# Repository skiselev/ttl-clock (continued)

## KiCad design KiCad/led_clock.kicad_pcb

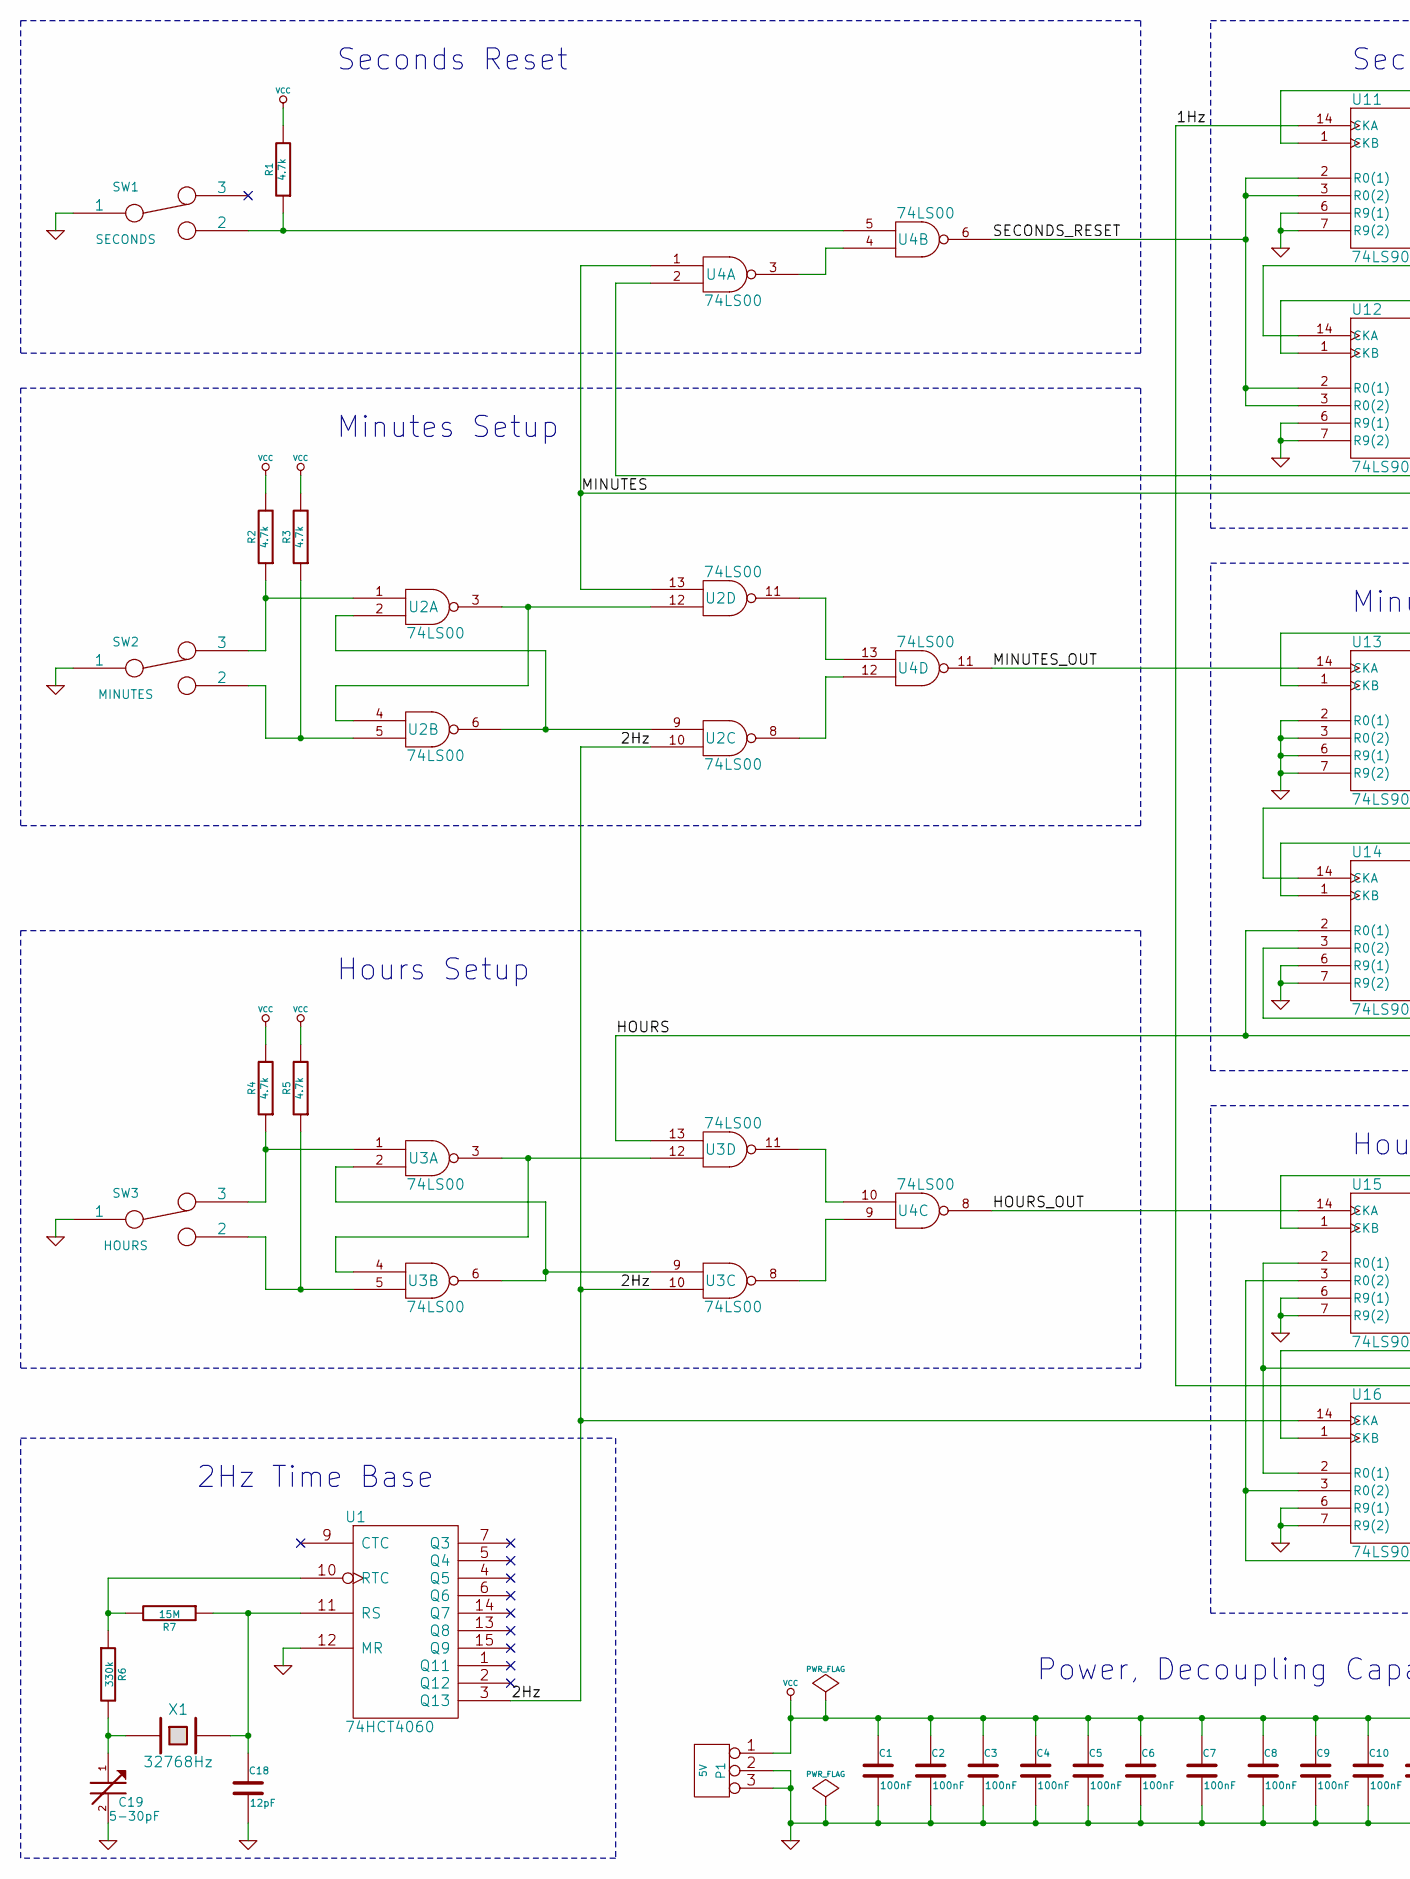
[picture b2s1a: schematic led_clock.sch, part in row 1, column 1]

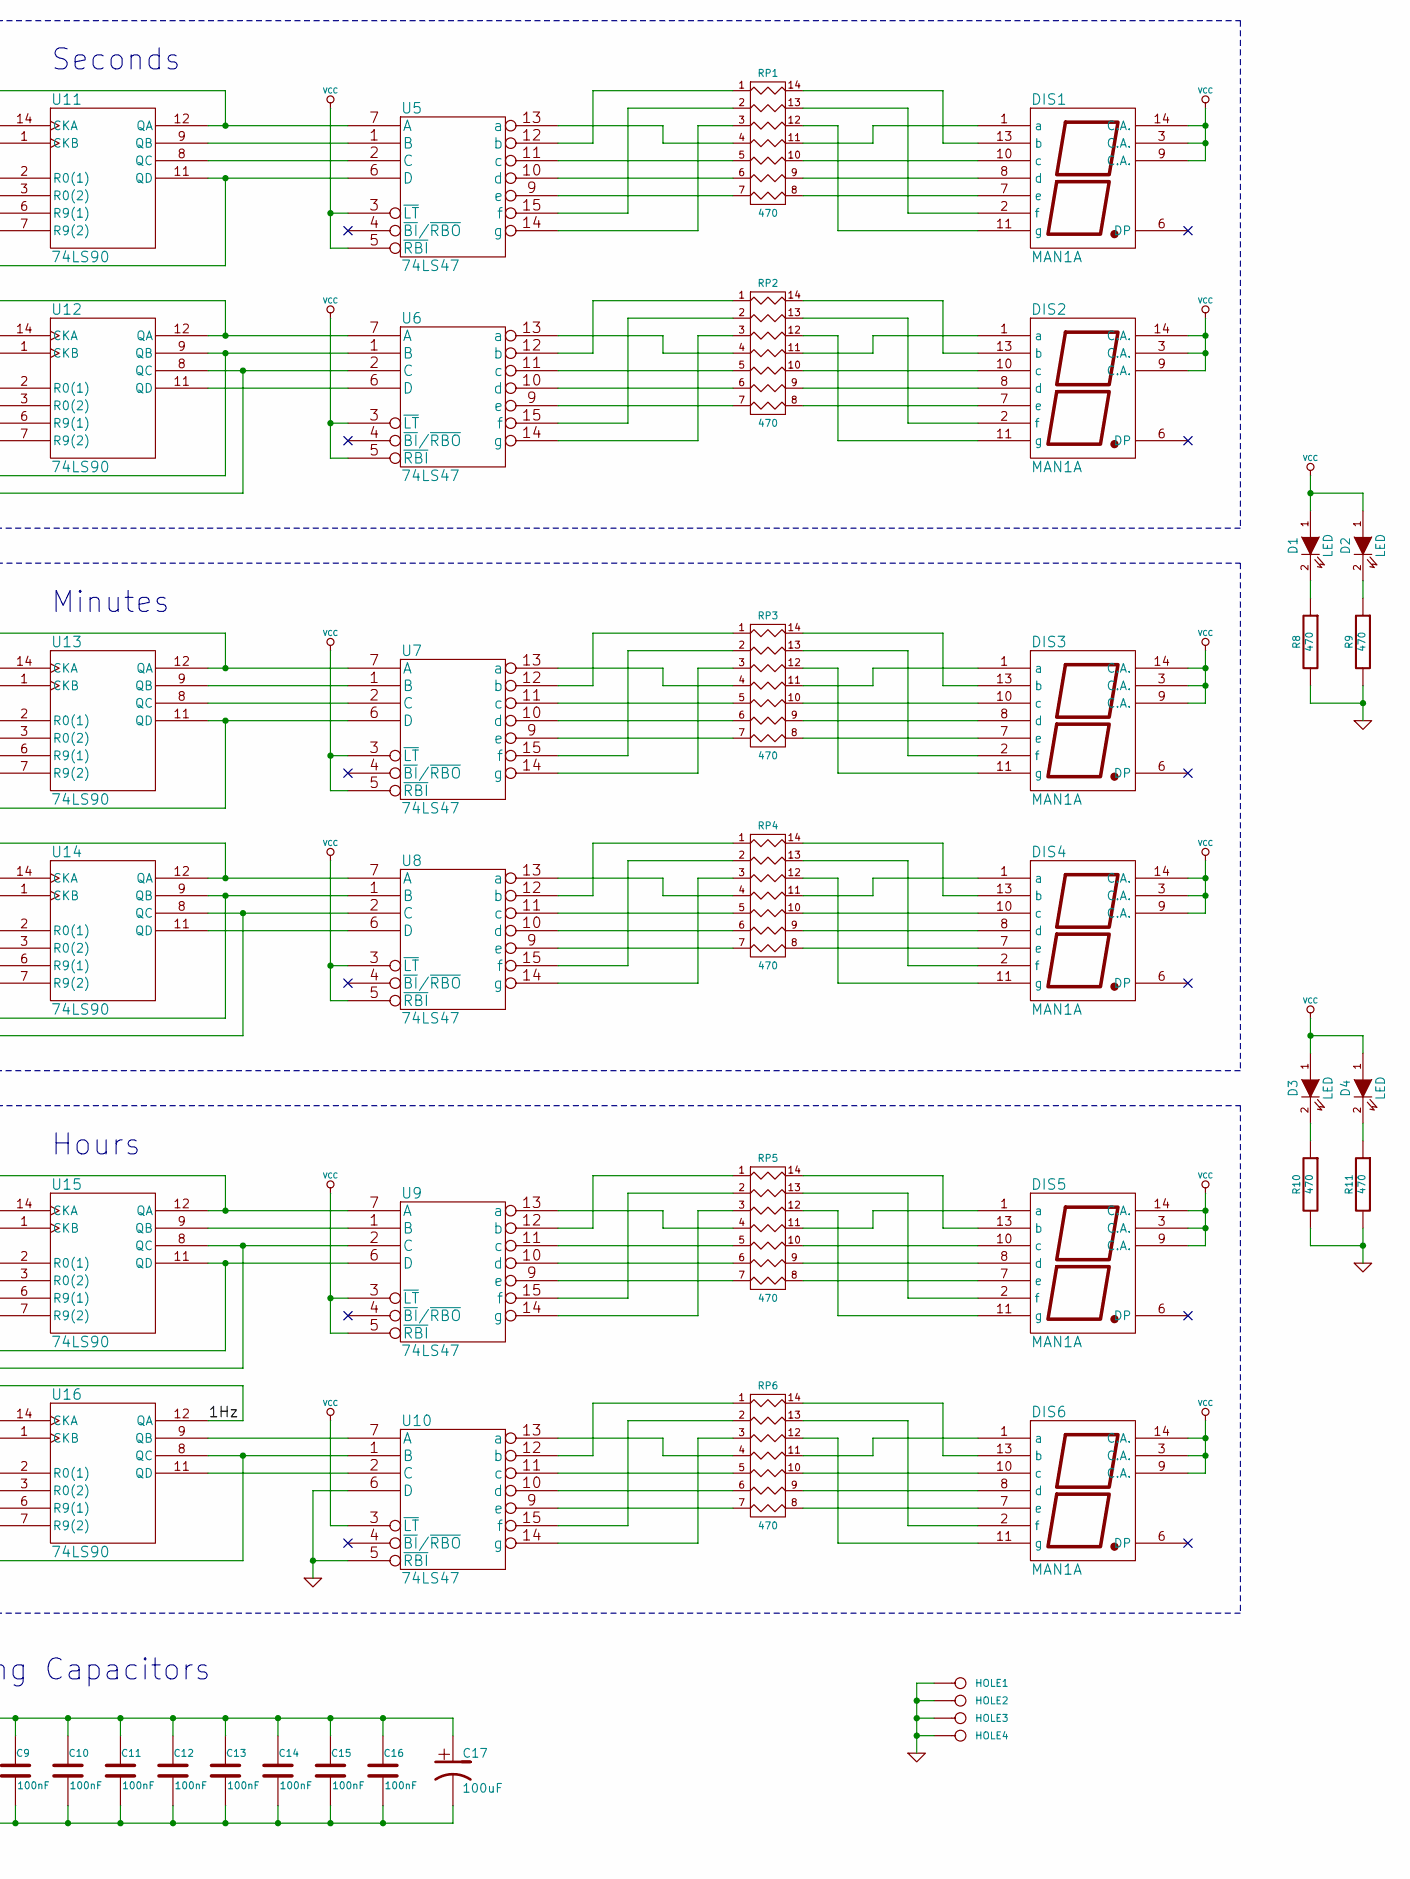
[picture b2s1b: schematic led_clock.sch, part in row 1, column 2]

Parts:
C1, C2, C3, C4, C5, C6, C7, C8, C9, C10, C11, C12, C13, C14, C15, C16: 100nF
C17: 100uF
C18: 12pF
C19: 5-30pF
D1, D2, D3, D4: LED
DIS1, DIS2, DIS3, DIS4, DIS5, DIS6: MAN1A
HOLE1, HOLE2, HOLE3, HOLE4: CONN_1
P1: 5V
R1, R2, R3, R4, R5: 4.7k
R6: 330k
R7: 15M
R8, R9, R10, R11: 470
RP1, RP2, RP3, RP4, RP5, RP6: 470
SW1: SECONDS
SW2: MINUTES
SW3: HOURS
U1: 74HCT4060
U2, U3, U4: 74LS00
U5, U6, U7, U8, U9, U10: 74LS47
U11, U12, U13, U14, U15, U16: 74LS90
X1: 32768Hz

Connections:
/1Hz: U11.14 (CKA), U16.12 (QA)
/2Hz: U1.3 (Q13), U2.10, U3.10, U16.14 (CKA)
/HOURS: U3.13, U8.2 (C), U14.2 (R0(1)), U14.8 (QC)
/HOURS_OUT: U4.8, U15.14 (CKA)
/MINUTES: U2.13, U4.1, U6.2 (C), U12.8 (QC)
/MINUTES_OUT: U4.11, U13.14 (CKA)
/SECONDS_RESET: U4.6, U11.2 (R0(1)), U11.3 (R0(2)), U12.2 (R0(1)), U12.3 (R0(2))
GND: C1.2, C2.2, C3.2, C4.2, C5.2, C6.2, C7.2, C8.2, C9.2, C10.2, C11.2, C12.2, C13.2, C14.2, C15.2, C16.2, C17.2, C18.2, C19.2, HOLE1.1, HOLE2.1, HOLE3.1, HOLE4.1, P1.2 (PM), P1.3, R8.2, R9.2, R10.2, R11.2, SW1.1, SW2.1, SW3.1, U1.8 (GND), U1.12 (MR), U2.7 (GND), U3.7 (GND), U4.7 (GND), U5.8 (GND), U6.8 (GND), U7.8 (GND), U8.8 (GND), U9.8 (GND), U10.5 (~RBI), U10.6 (D), U10.8 (GND), U11.6 (R9(1)), U11.7 (R9(2)), U11.10 (GND), U12.6 (R9(1)), U12.7 (R9(2)), U12.10 (GND), U13.2 (R0(1)), U13.3 (R0(2)), U13.6 (R9(1)), U13.7 (R9(2)), U13.10 (GND), U14.6 (R9(1)), U14.7 (R9(2)), U14.10 (GND), U15.6 (R9(1)), U15.7 (R9(2)), U15.10 (GND), U16.6 (R9(1)), U16.7 (R9(2)), U16.10 (GND)
unnamed: U3.3, U3.4, U3.12
unnamed: R4.1, SW3.3, U3.1
unnamed: U3.2, U3.6, U3.9
unnamed: R6.1, R7.2, U1.10 (RTC)
unnamed: U3.8, U4.9
unnamed: U3.11, U4.10
unnamed: U9.6 (D), U15.11 (QD), U16.1 (CKB)
unnamed: U10.1 (B), U15.3 (R0(2)), U16.3 (R0(2)), U16.8 (QC)
unnamed: U9.2 (C), U15.2 (R0(1)), U15.8 (QC), U16.2 (R0(1))
unnamed: U2.8, U4.12
unnamed: U2.11, U4.13
unnamed: U2.2, U2.6, U2.9
unnamed: C18.1, R7.1, U1.11 (RS), X1.2
unnamed: C19.1, R6.2, X1.1
unnamed: U4.3, U4.4
unnamed: R1.1, SW1.2, U4.5
unnamed: U10.2 (C), U16.11 (QD)
unnamed: U7.1 (B), U13.9 (QB)
unnamed: U6.6 (D), U12.11 (QD)
unnamed: U5.2 (C), U11.8 (QC)
unnamed: U5.1 (B), U11.9 (QB)
unnamed: U7.2 (C), U13.8 (QC)
unnamed: U10.7 (A), U16.9 (QB)
unnamed: U8.7 (A), U14.1 (CKB), U14.12 (QA)
unnamed: U9.7 (A), U15.1 (CKB), U15.12 (QA)
unnamed: U9.1 (B), U15.9 (QB)
unnamed: U8.6 (D), U14.11 (QD)
unnamed: U7.6 (D), U13.11 (QD), U14.14 (CKA)
unnamed: U5.6 (D), U11.11 (QD), U12.14 (CKA)
unnamed: U6.7 (A), U12.1 (CKB), U12.12 (QA)
unnamed: U2.3, U2.4, U2.12
unnamed: U5.7 (A), U11.1 (CKB), U11.12 (QA)
unnamed: U7.7 (A), U13.1 (CKB), U13.12 (QA)
unnamed: R2.1, SW2.3, U2.1
unnamed: RP5.3, U9.14 (g)
unnamed: RP5.1, U9.12 (b)
unnamed: RP5.7, U9.9 (e)
unnamed: RP5.2, U9.15 (f)
unnamed: RP5.6, U9.10 (d)
unnamed: RP5.5, U9.11 (c)
unnamed: RP5.4, U9.13 (a)
unnamed: RP4.4, U8.13 (a)
unnamed: RP4.3, U8.14 (g)
unnamed: RP4.2, U8.15 (f)
unnamed: RP4.1, U8.12 (b)
unnamed: RP4.7, U8.9 (e)
unnamed: RP6.5, U10.11 (c)
unnamed: RP6.4, U10.13 (a)
unnamed: RP6.3, U10.14 (g)
unnamed: RP6.2, U10.15 (f)
unnamed: RP6.1, U10.12 (b)
unnamed: RP6.7, U10.9 (e)
unnamed: RP6.6, U10.10 (d)
unnamed: RP4.6, U8.10 (d)
unnamed: DIS2.8 (d), RP2.9 (R8)
unnamed: RP3.4, U7.13 (a)
unnamed: DIS2.1 (a), RP2.11 (R6)
unnamed: DIS2.11 (g), RP2.12 (R5)
unnamed: DIS2.2 (f), RP2.13 (R4)
unnamed: DIS2.13 (b), RP2.14 (R3)
unnamed: DIS2.7 (e), RP2.8
unnamed: DIS2.10 (c), RP2.10 (R7)
unnamed: RP2.4, U6.13 (a)
unnamed: RP3.2, U7.15 (f)
unnamed: RP4.5, U8.11 (c)
unnamed: RP3.3, U7.14 (g)
unnamed: DIS3.1 (a), RP3.11 (R6)
unnamed: RP3.1, U7.12 (b)
unnamed: RP3.7, U7.9 (e)
unnamed: RP3.6, U7.10 (d)
unnamed: RP3.5, U7.11 (c)
unnamed: DIS6.11 (g), RP6.12 (R5)
unnamed: DIS6.2 (f), RP6.13 (R4)
unnamed: DIS6.13 (b), RP6.14 (R3)
unnamed: DIS6.7 (e), RP6.8
unnamed: DIS6.8 (d), RP6.9 (R8)
unnamed: DIS6.10 (c), RP6.10 (R7)
unnamed: DIS6.1 (a), RP6.11 (R6)
unnamed: DIS5.1 (a), RP5.11 (R6)
unnamed: DIS5.11 (g), RP5.12 (R5)
unnamed: DIS5.2 (f), RP5.13 (R4)
unnamed: DIS5.13 (b), RP5.14 (R3)
unnamed: DIS5.7 (e), RP5.8
unnamed: DIS3.13 (b), RP3.14 (R3)
unnamed: DIS4.2 (f), RP4.13 (R4)
unnamed: DIS4.13 (b), RP4.14 (R3)
unnamed: DIS3.11 (g), RP3.12 (R5)
unnamed: DIS3.2 (f), RP3.13 (R4)
unnamed: DIS3.7 (e), RP3.8
unnamed: DIS3.8 (d), RP3.9 (R8)
unnamed: DIS3.10 (c), RP3.10 (R7)
unnamed: DIS4.1 (a), RP4.11 (R6)
unnamed: DIS5.8 (d), RP5.9 (R8)
unnamed: DIS5.10 (c), RP5.10 (R7)
unnamed: DIS4.11 (g), RP4.12 (R5)
unnamed: DIS4.7 (e), RP4.8
unnamed: DIS4.8 (d), RP4.9 (R8)
unnamed: DIS4.10 (c), RP4.10 (R7)
unnamed: U4.2, U6.1 (B), U12.9 (QB)
unnamed: U8.1 (B), U14.3 (R0(2)), U14.9 (QB)
unnamed: R3.1, SW2.2, U2.5
unnamed: R5.1, SW3.2, U3.5
unnamed: D4.2 (K), R11.1
unnamed: D3.2 (K), R10.1
unnamed: D2.2 (K), R9.1
unnamed: D1.2 (K), R8.1
unnamed: DIS1.2 (f), RP1.13 (R4)
unnamed: RP1.3, U5.14 (g)
unnamed: DIS1.13 (b), RP1.14 (R3)
unnamed: RP1.2, U5.15 (f)
unnamed: RP1.1, U5.12 (b)
unnamed: DIS1.7 (e), RP1.8
unnamed: DIS1.8 (d), RP1.9 (R8)
unnamed: DIS1.10 (c), RP1.10 (R7)
unnamed: DIS1.11 (g), RP1.12 (R5)
unnamed: RP1.7, U5.9 (e)
unnamed: RP1.6, U5.10 (d)
unnamed: RP1.5, U5.11 (c)
unnamed: RP2.3, U6.14 (g)
unnamed: RP2.2, U6.15 (f)
unnamed: RP2.1, U6.12 (b)
unnamed: RP2.7, U6.9 (e)
unnamed: RP2.6, U6.10 (d)
unnamed: RP2.5, U6.11 (c)
unnamed: DIS1.1 (a), RP1.11 (R6)
unnamed: RP1.4, U5.13 (a)
VCC: C1.1, C2.1, C3.1, C4.1, C5.1, C6.1, C7.1, C8.1, C9.1, C10.1, C11.1, C12.1, C13.1, C14.1, C15.1, C16.1, C17.1, D1.1 (A), D2.1 (A), D3.1 (A), D4.1 (A), DIS1.3 (C.A.), DIS1.9 (C.A.), DIS1.14 (C.A.), DIS2.3 (C.A.), DIS2.9 (C.A.), DIS2.14 (C.A.), DIS3.3 (C.A.), DIS3.9 (C.A.), DIS3.14 (C.A.), DIS4.3 (C.A.), DIS4.9 (C.A.), DIS4.14 (C.A.), DIS5.3 (C.A.), DIS5.9 (C.A.), DIS5.14 (C.A.), DIS6.3 (C.A.), DIS6.9 (C.A.), DIS6.14 (C.A.), P1.1, R1.2, R2.2, R3.2, R4.2, R5.2, U1.16 (VCC), U2.14 (VCC), U3.14 (VCC), U4.14 (VCC), U5.3 (~LT), U5.5 (~RBI), U5.16 (VCC), U6.3 (~LT), U6.5 (~RBI), U6.16 (VCC), U7.3 (~LT), U7.5 (~RBI), U7.16 (VCC), U8.3 (~LT), U8.5 (~RBI), U8.16 (VCC), U9.3 (~LT), U9.5 (~RBI), U9.16 (VCC), U10.3 (~LT), U10.16 (VCC), U11.5 (VCC), U12.5 (VCC), U13.5 (VCC), U14.5 (VCC), U15.5 (VCC), U16.5 (VCC)

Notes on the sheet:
Seconds
Minutes
Hours
Power, Decoupling Capacitors
2Hz Time Base
Hours Setup
Minutes Setup
Seconds Reset

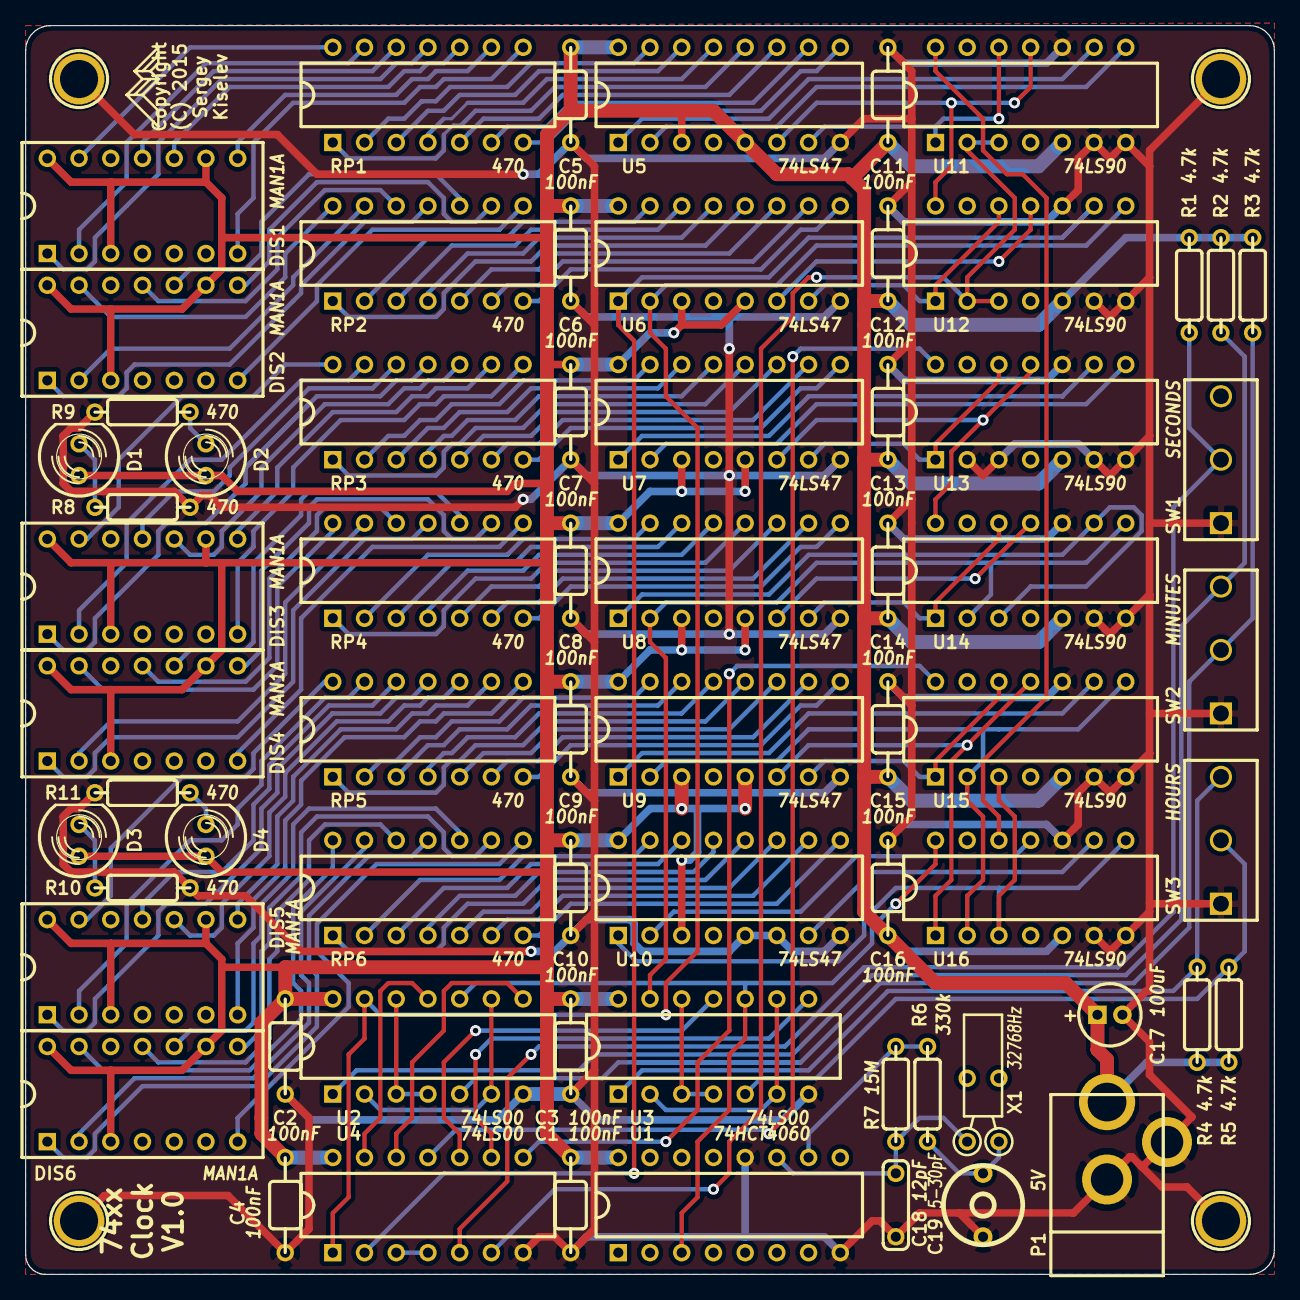
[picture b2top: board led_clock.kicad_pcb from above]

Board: 2 copper layers, 100.0 x 100.0 mm, 71 parts (0 on the bottom side), 135 nets.

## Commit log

2020-12-03 README: Add links to the components
2020-12-03 README: Update links to design files
2020-12-03 README: Update links
2020-12-03 Upload files
2020-12-03 README: Formatting
2020-12-03 Fix JPG extensions case
2020-12-04 Replace design files with version 1.1
2020-12-04 README: Update parts for PCB version 1.1
2020-12-04 README: Update Mouser project link
2020-12-04 README: BOM Fixes
2020-12-08 README: Fix the displays references
2020-12-08 Add photos for version 1.1
2020-12-08 Assembly_Instructions: Formatting
2020-12-09 Assembly_Instructions: More formatting
2020-12-11 Assembly_Instructions: Fix typos
